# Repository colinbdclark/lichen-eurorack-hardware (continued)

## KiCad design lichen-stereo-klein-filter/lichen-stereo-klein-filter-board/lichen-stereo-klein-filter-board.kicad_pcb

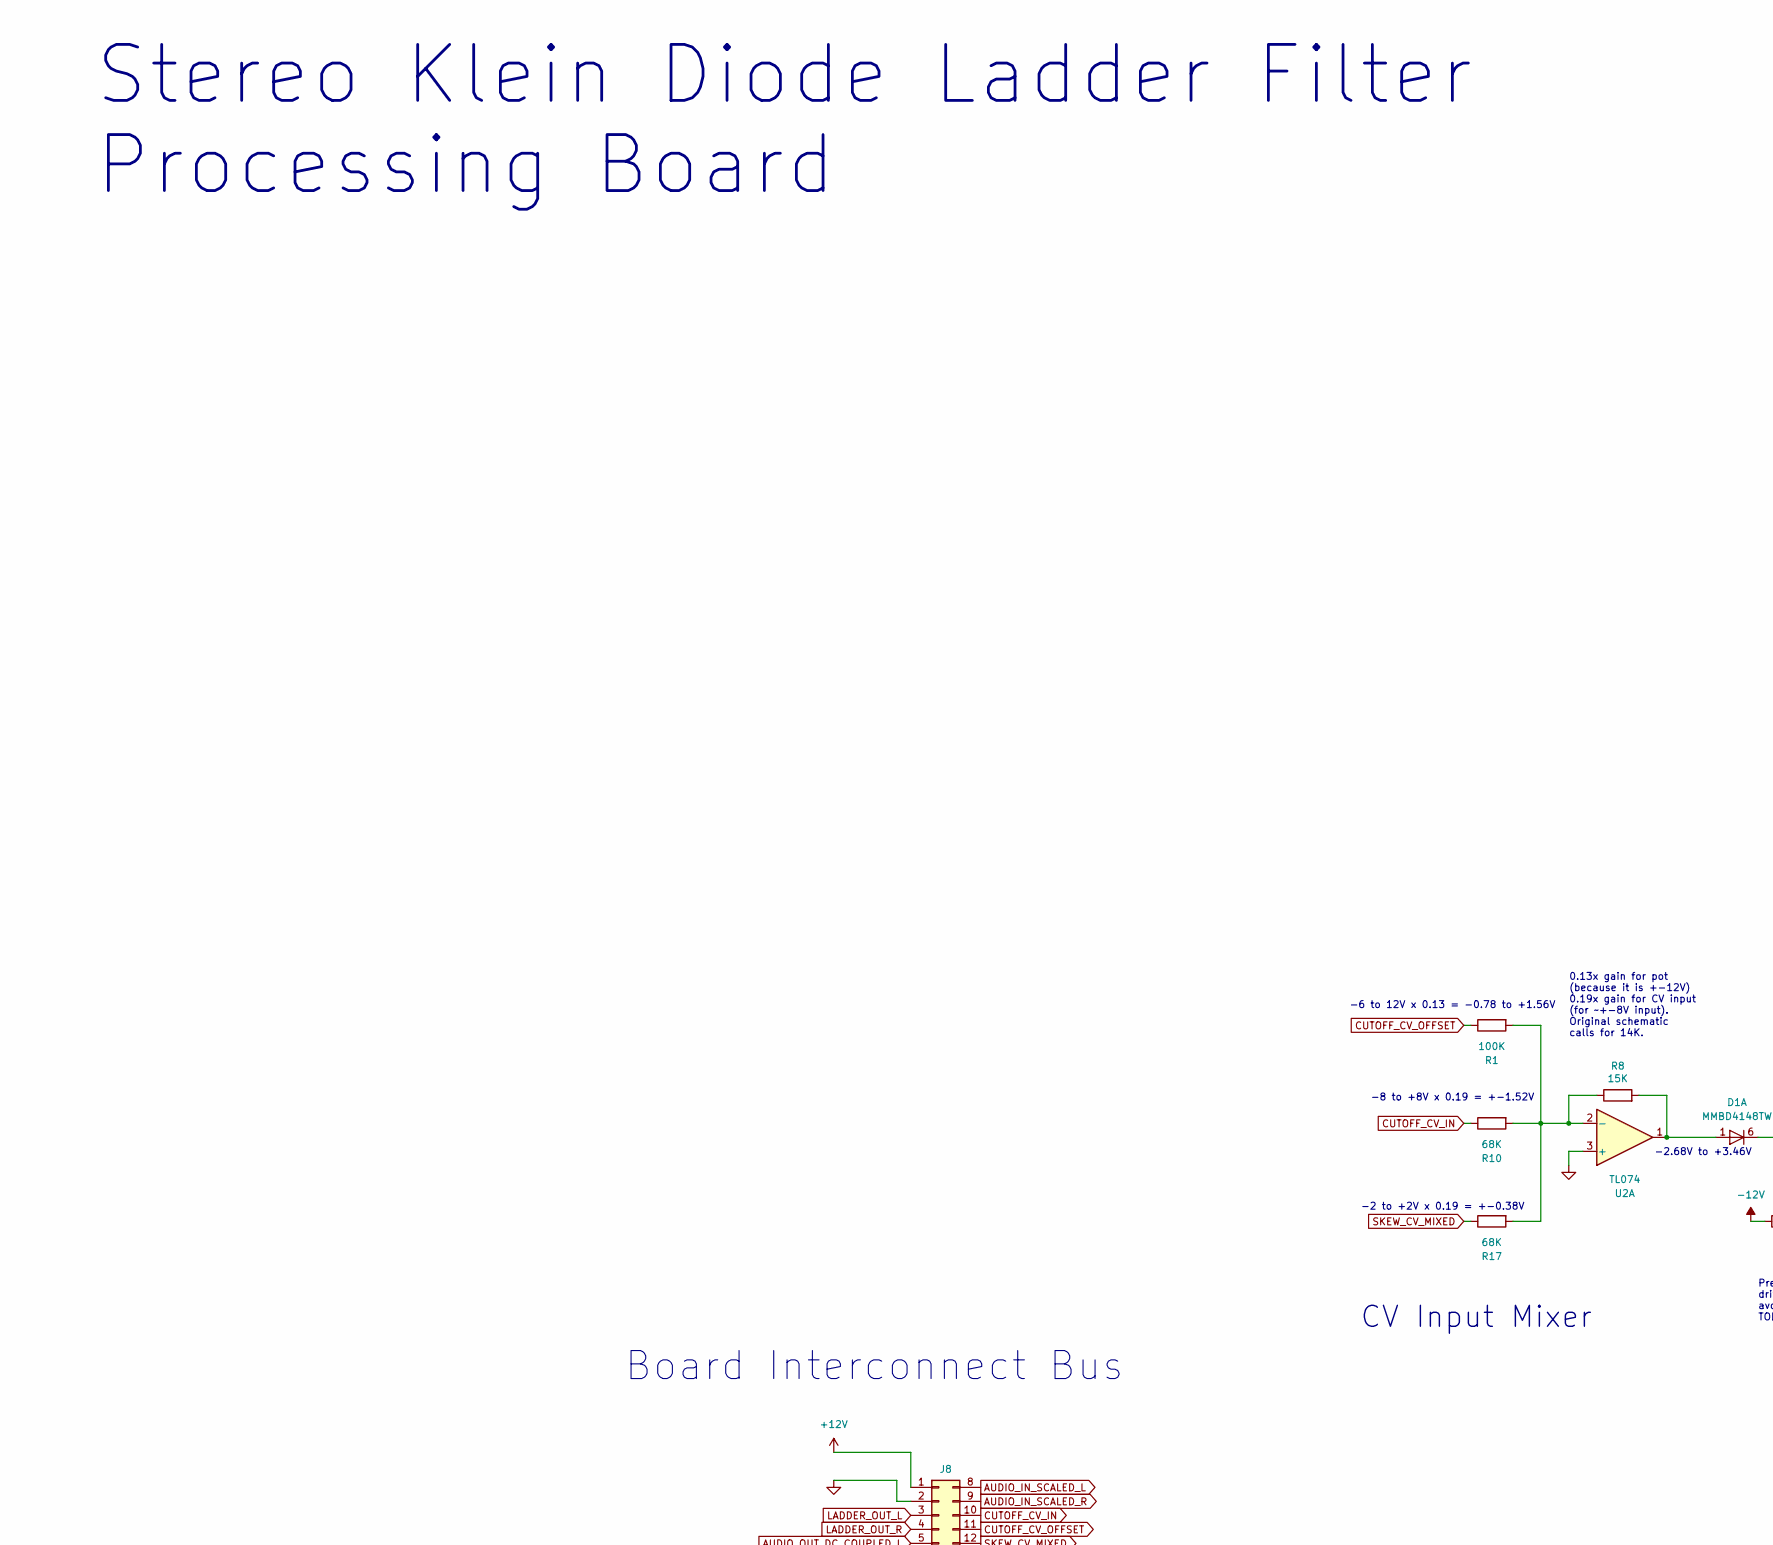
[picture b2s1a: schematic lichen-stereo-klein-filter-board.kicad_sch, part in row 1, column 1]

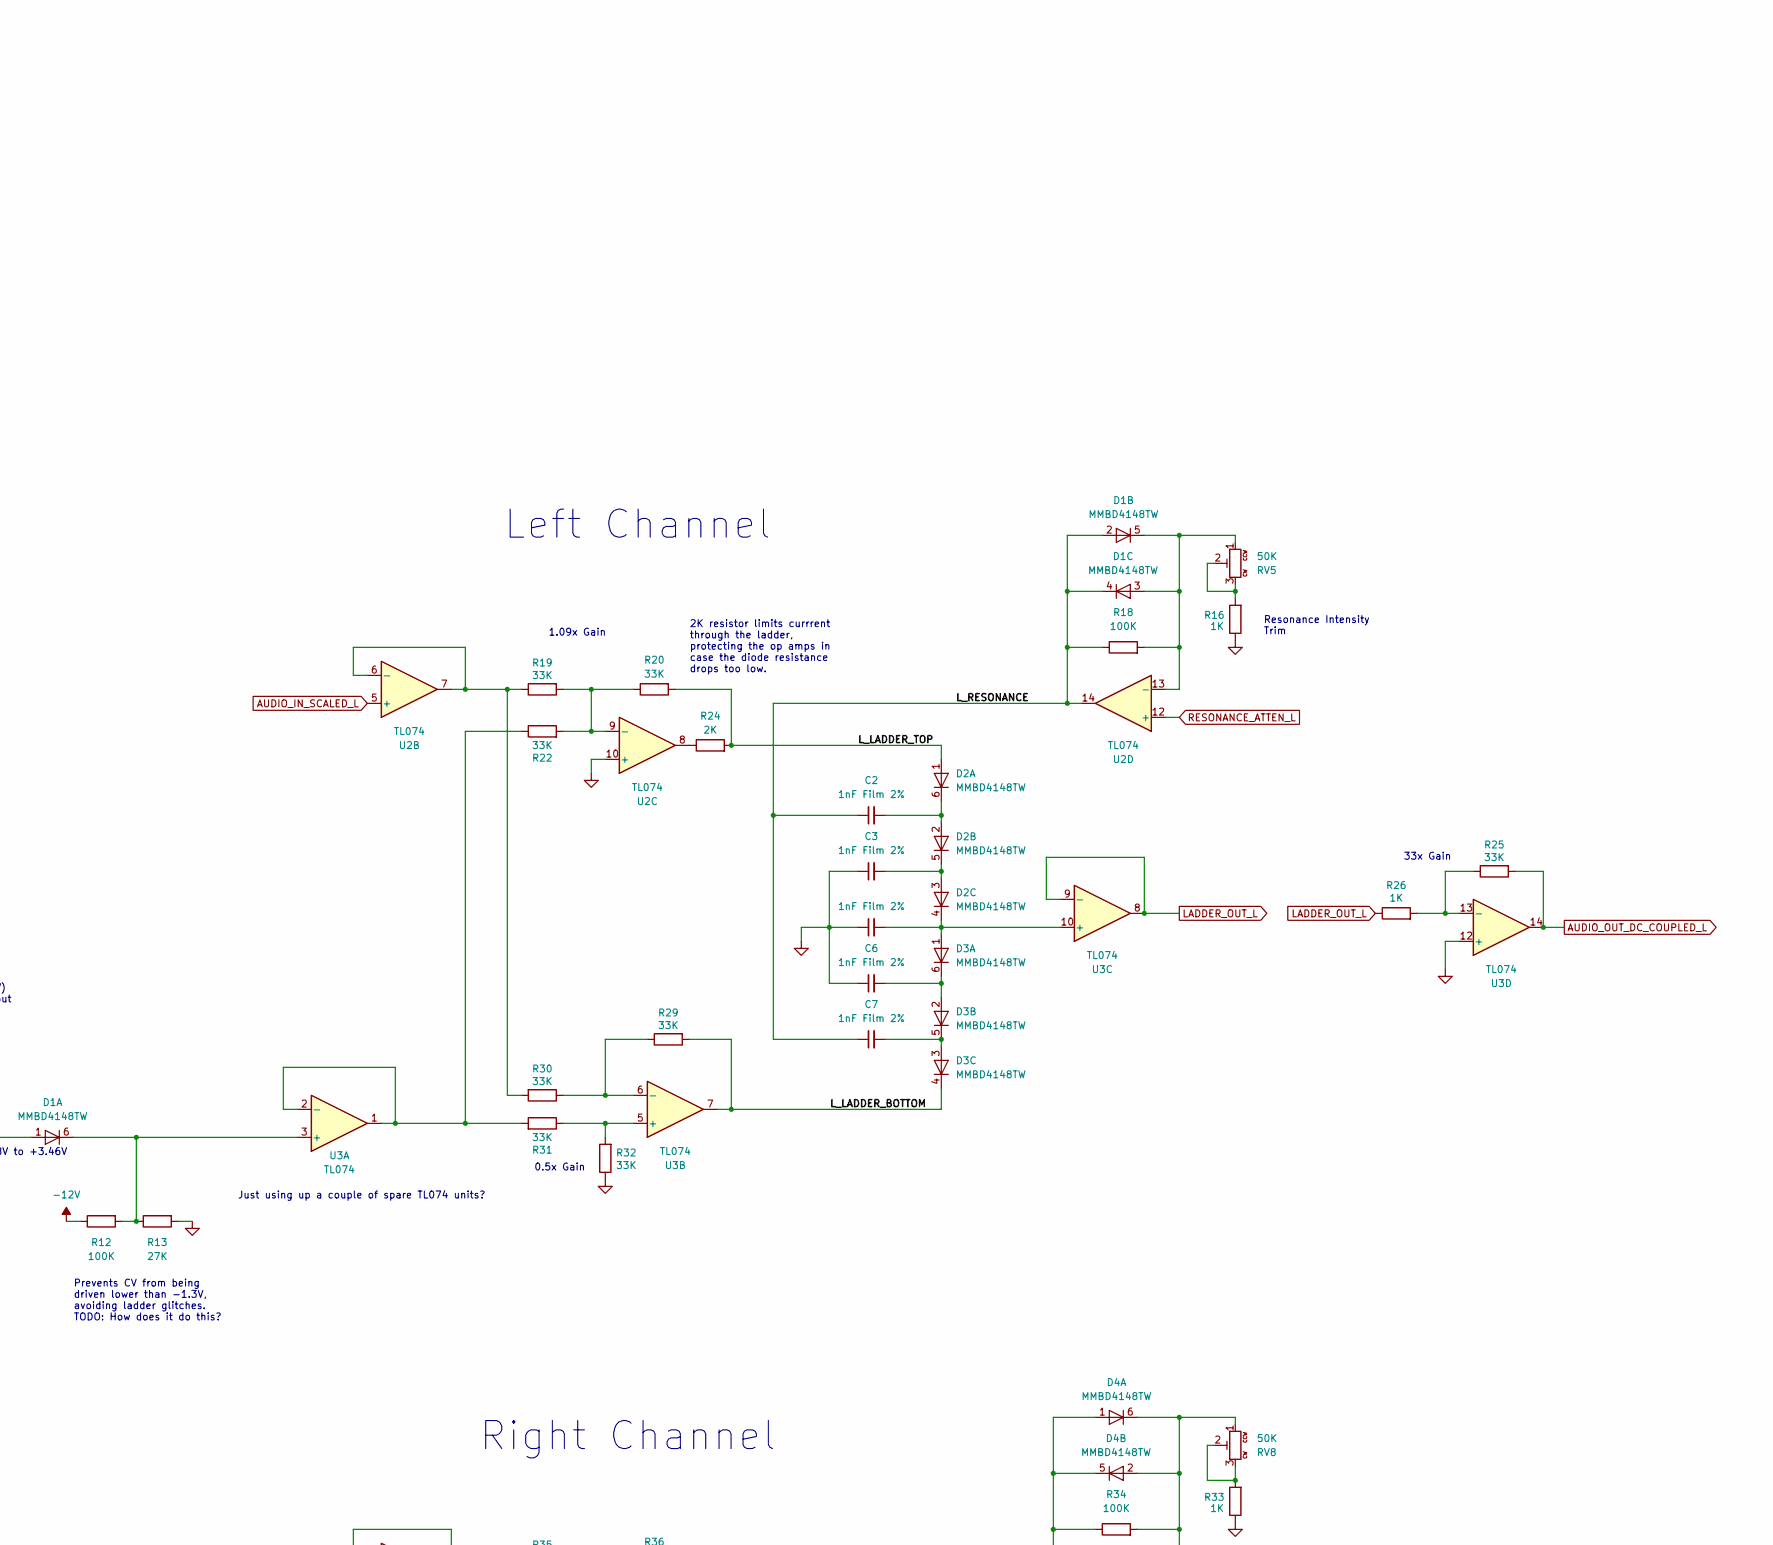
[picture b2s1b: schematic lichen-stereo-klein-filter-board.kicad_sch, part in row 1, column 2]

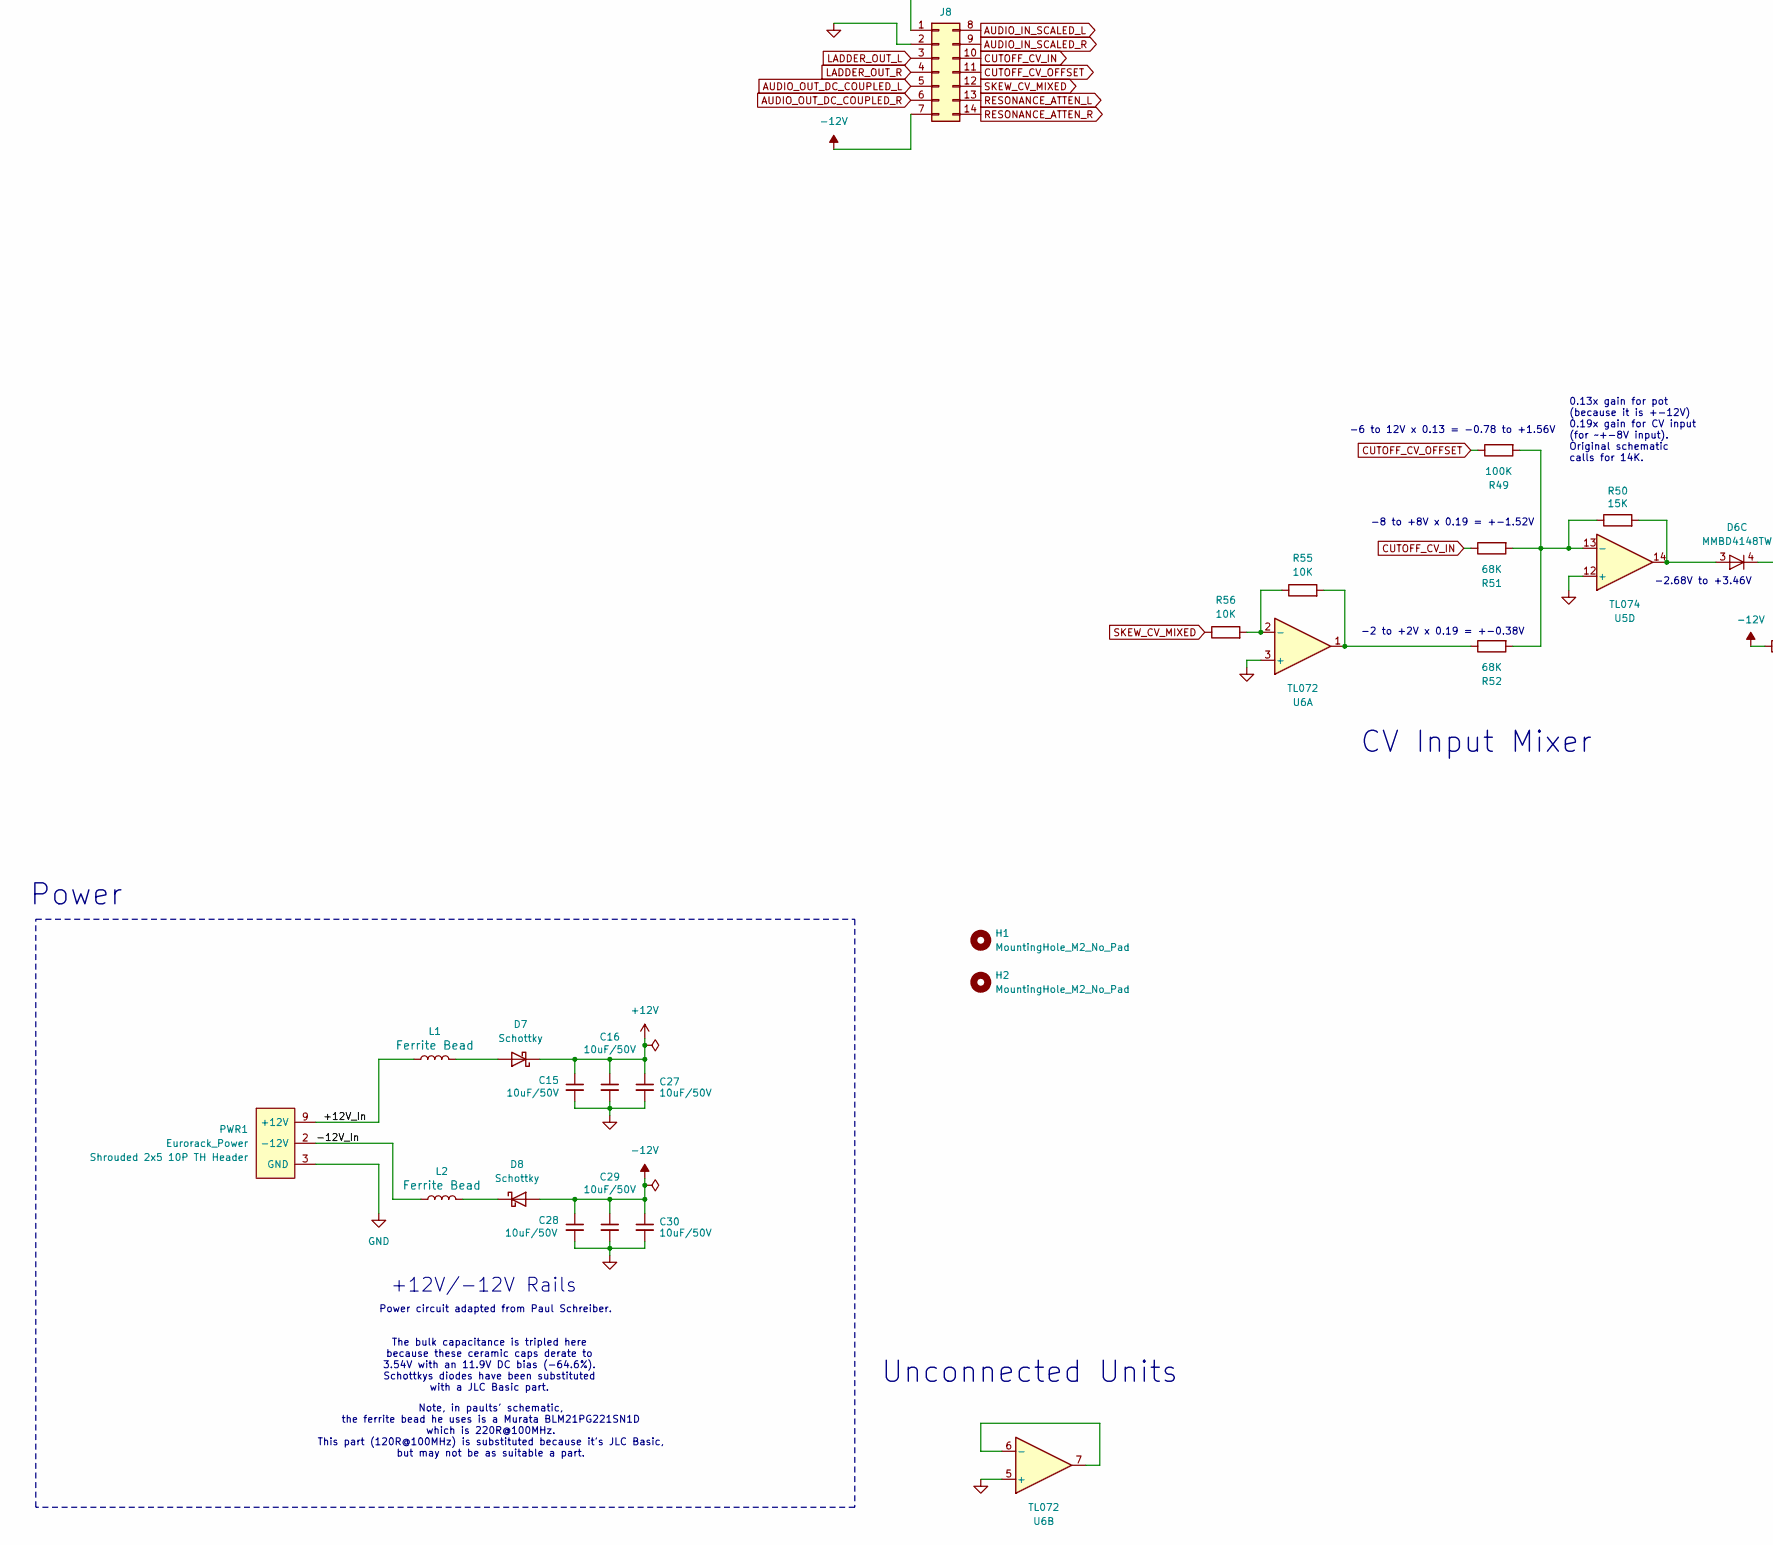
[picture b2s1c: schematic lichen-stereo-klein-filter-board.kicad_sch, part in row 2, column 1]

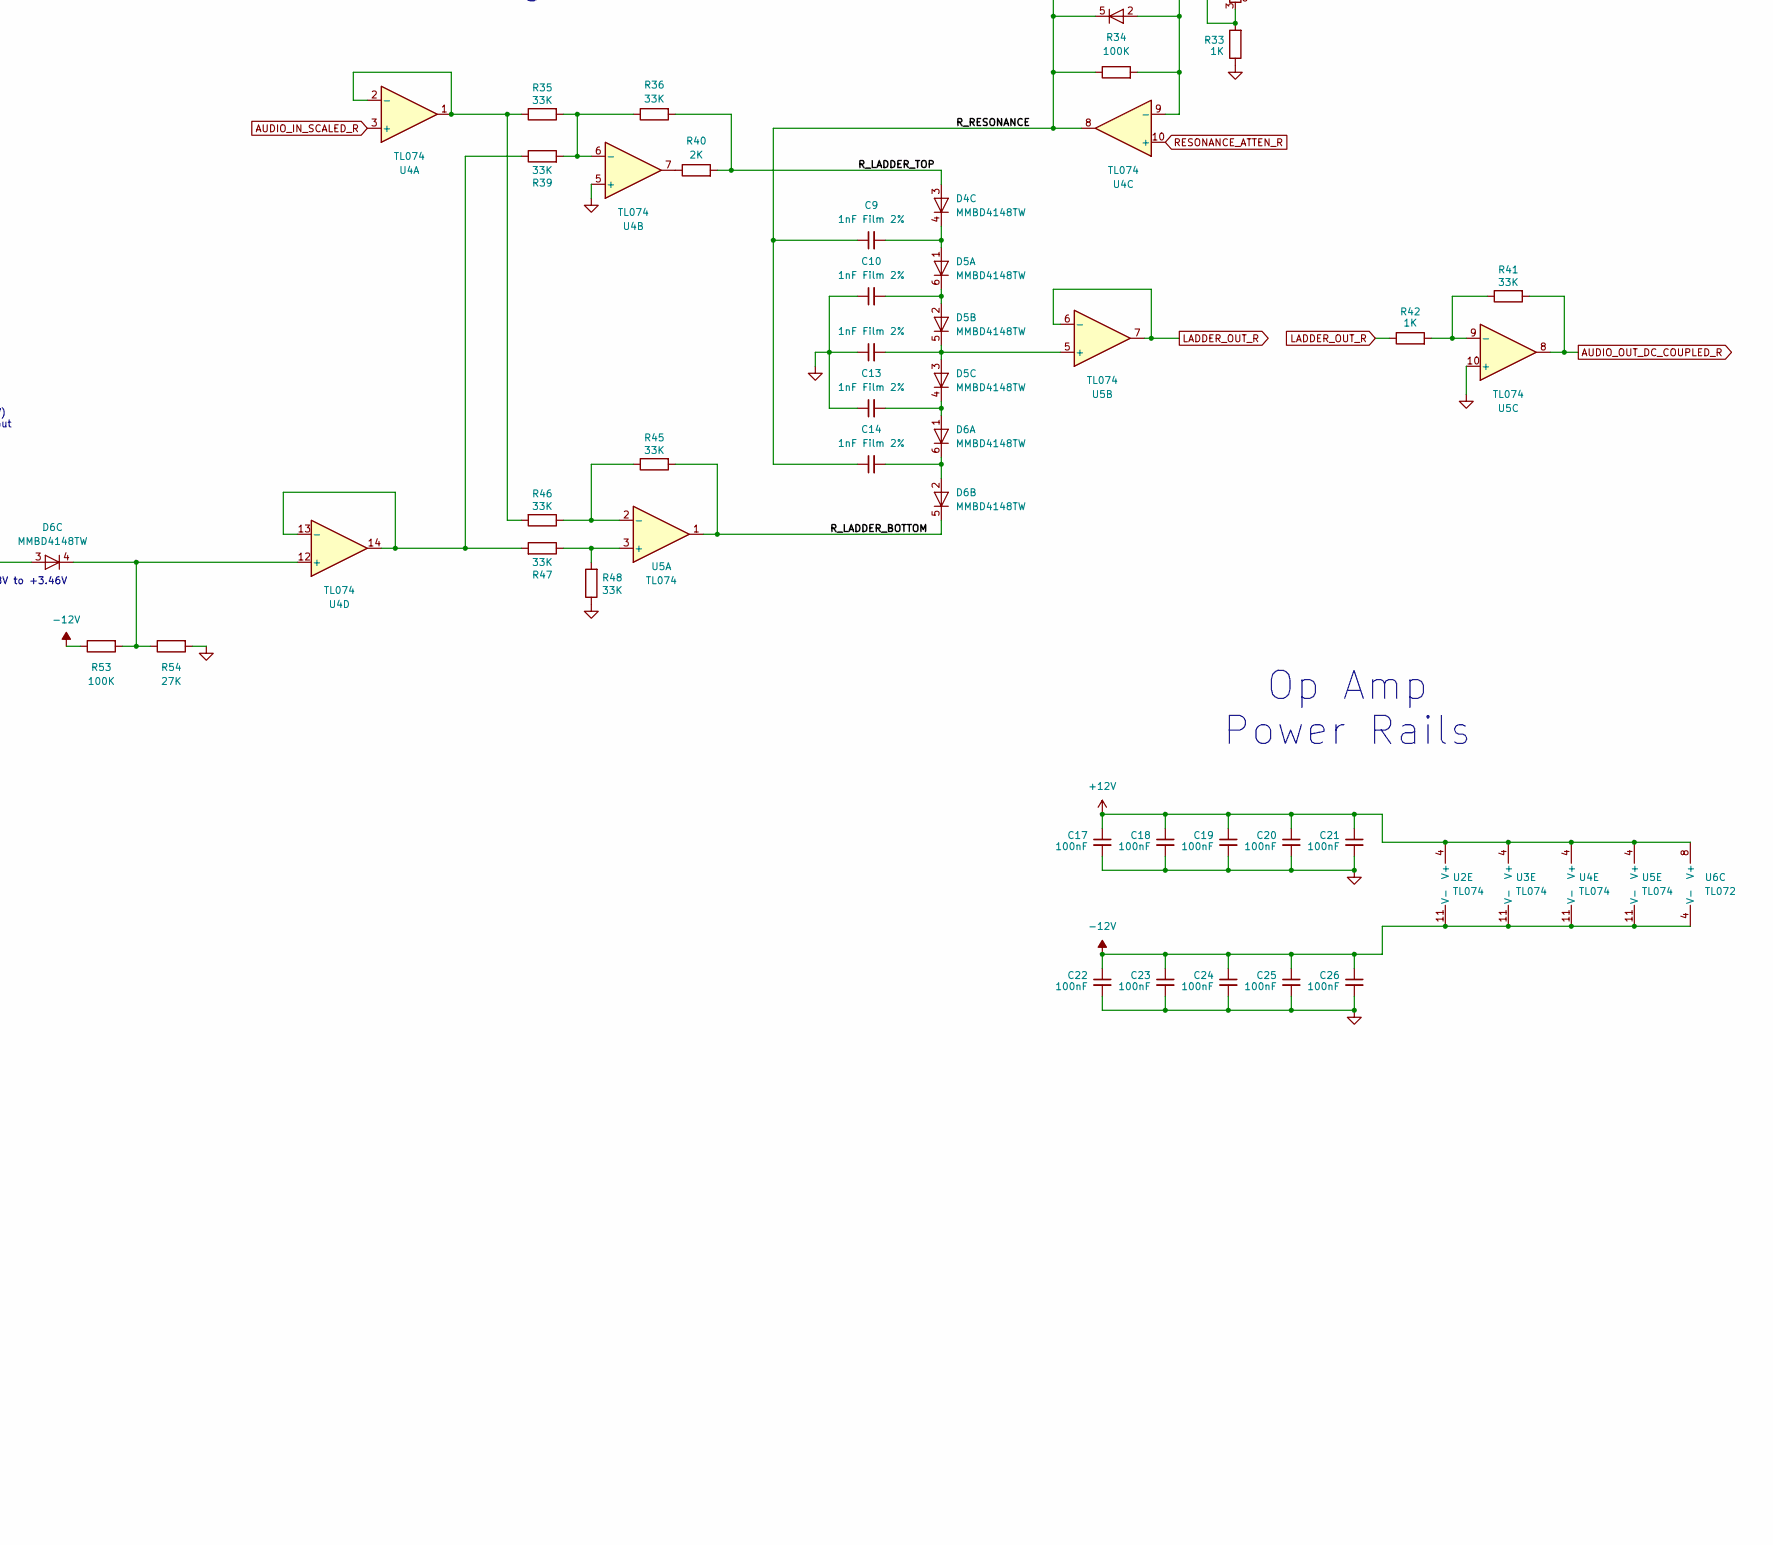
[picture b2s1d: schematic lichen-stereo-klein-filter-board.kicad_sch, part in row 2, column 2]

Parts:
C2, C3, C4, C6, C7, C9, C10, C11, C13, C14: 1nF; C_0805; Part Number ECHU1H102GX5; LCSC C569826
C15, C16, C27, C28, C29, C30: 10uF; C_1206_3216Metric; Part Number CL31A106KBHNNNE; LCSC C13585
C17, C18, C19, C20, C21, C22, C23, C24, C25, C26: 100nF; C_0402_1005Metric_small_pads; Part Number CL05B104KB54PNC; LCSC C307331
D1, D2, D3, D4, D5, D6: MMBD4148TW; SOT-363_SC-70-6; Part Number MMBD4148TW; LCSC C5240652
D7, D8: Schottky; D_SMA_Handsoldering; Part Number SS34; LCSC C8678
H1, H2: MountingHole_M2_No_Pad; MountingHole_2.2mm_M2
J8: 02x07 Pins; PinHeader_2x07_P2.54mm_Vertical_SMD; Part Number 2.54-2*7P针立贴; LCSC C84004
L1, L2: FerriteBead_0603_2A; R_0603; Part Number BLM18PG121SN1D; LCSC C14709
PWR1: Eurorack_Power; Eurorack_Power_Shrouded_TH_Staggered_Small
R1, R12, R18, R34, R49, R53: 100K; R_0603; Part Number 0603WAF1003T5E; LCSC C25803
R8, R50: 15K; R_0603; Part Number 0603WAF1502T5E; LCSC C22809
R10, R17, R51, R52: 68K; R_0603; Part Number 0603WAF6802T5E; LCSC C23231
R13, R54: 27K; R_0603; Part Number 0603WAF2702T5E; LCSC C22967
R16, R26, R33, R42: 1K; R_0603; Part Number 0603WAF1001T5E; LCSC C21190
R19, R20, R22, R25, R29, R30, R31, R32, R35, R36, R39, R41, R45, R46, R47, R48: 33K; R_0603; Part Number 0603WAF3302T5E; LCSC C4216
R24, R40: 2K; R_0603; Part Number 0603WAF2001T5E; LCSC C22975
R55, R56: 10K; R_0603; Part Number 0603WAF1002T5E; LCSC C25804
RV5, RV8: 50K; Potentiometer_Bourns_3266W_Vertical; Part Number 3266W-1-503LF; LCSC C780226
U2, U3, U4, U5: TL074; SOIC-14_3.9x8.7mm_P1.27mm; Part Number TL074IDR; LCSC C6964
U6: TL072; SOIC-8_3.9x4.9mm_P1.27mm; Part Number TL072CDT; LCSC C6961

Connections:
+12V: C15.1, C16.1, C17.1, C18.1, C19.1, C20.1, C21.1, C27.1, D7.1 (K), J8.1, U2.4 (V+), U3.4 (V+), U4.4 (V+), U5.4 (V+), U6.8 (V+)
-12V: C22.1, C23.1, C24.1, C25.1, C26.1, C28.1, C29.1, C30.1, D8.2 (A), J8.7, R12.1, R53.1, U2.11 (V-), U3.11 (V-), U4.11 (V-), U5.11 (V-), U6.4 (V-)
/+12V_In: L1.1, PWR1.9 (+12V), PWR1.10 (+12V)
/-12V_In: L2.1, PWR1.1 (-12V), PWR1.2 (-12V)
/L_LADDER_BOTTOM: D3.4 (K), R29.2, U3.7
/L_LADDER_TOP: D2.1 (A), R20.2, R24.2
/L_RESONANCE: C2.1, C7.1, D1.2 (A), D1.4 (K), R18.1, U2.14
/R_LADDER_BOTTOM: D6.5 (K), R45.2, U5.1
/R_LADDER_TOP: D4.3 (A), R36.2, R40.2
/R_RESONANCE: C9.1, C14.1, D4.1 (A), D4.5 (K), R34.1, U4.8
AUDIO_IN_SCALED_L: J8.8, U2.5 (+)
AUDIO_IN_SCALED_R: J8.9, U4.3 (+)
AUDIO_OUT_DC_COUPLED_L: J8.5, R25.2, U3.14
AUDIO_OUT_DC_COUPLED_R: J8.6, R41.2, U5.8
CUTOFF_CV_IN: J8.10, R10.1, R51.1
CUTOFF_CV_OFFSET: J8.11, R1.1, R49.1
GND: C3.1, C4.1, C6.1, C10.1, C11.1, C13.1, C15.2, C16.2, C17.2, C18.2, C19.2, C20.2, C21.2, C22.2, C23.2, C24.2, C25.2, C26.2, C27.2, C28.2, C29.2, C30.2, J8.2, PWR1.3 (GND), PWR1.4 (GND), PWR1.5 (GND), PWR1.6 (GND), PWR1.7 (GND), PWR1.8 (GND), R13.2, R16.1, R32.1, R33.1, R48.1, R54.2, U2.3 (+), U2.10 (+), U3.12 (+), U4.5 (+), U5.10 (+), U5.12 (+), U6.3 (+), U6.5 (+)
LADDER_OUT_L: J8.3, R26.1, U3.8, U3.9 (-)
LADDER_OUT_R: J8.4, R42.1, U5.6 (-), U5.7
unnamed: D1.1 (A), R8.2, U2.1
unnamed: D1.6 (K), R12.2, R13.1, U3.3 (+)
unnamed: D1.3 (A), D1.5 (K), R18.2, RV5.1, U2.13 (-)
unnamed: C2.2, D2.2 (A), D2.6 (K)
unnamed: C3.2, D2.3 (A), D2.5 (K)
unnamed: C4.2, D2.4 (K), D3.1 (A), U3.10 (+)
unnamed: C6.2, D3.2 (A), D3.6 (K)
unnamed: C7.2, D3.3 (A), D3.5 (K)
unnamed: D4.2 (A), D4.6 (K), R34.2, RV8.1, U4.9 (-)
unnamed: C9.2, D4.4 (K), D5.1 (A)
unnamed: C10.2, D5.2 (A), D5.6 (K)
unnamed: C11.2, D5.3 (A), D5.5 (K), U5.5 (+)
unnamed: C13.2, D5.4 (K), D6.1 (A)
unnamed: C14.2, D6.2 (A), D6.6 (K)
unnamed: D6.3 (A), R50.2, U5.14
unnamed: D6.4 (K), R53.2, R54.1, U4.12 (+)
unnamed: D7.2 (A), L1.2
unnamed: D8.1 (K), L2.2
unnamed: R16.2, RV5.2, RV5.3
unnamed: R24.1, U2.8
unnamed: R33.2, RV8.2, RV8.3
unnamed: R40.1, U4.7
unnamed: R52.1, R55.2, U6.1
unnamed: R1.2, R8.1, R10.2, R17.2, U2.2 (-)
unnamed: R19.1, R30.2, U2.6 (-), U2.7
unnamed: R19.2, R20.1, R22.2, U2.9 (-)
unnamed: R22.1, R31.2, U3.1, U3.2 (-)
unnamed: R31.1, R32.2, U3.5 (+)
unnamed: R29.1, R30.1, U3.6 (-)
unnamed: R25.1, R26.2, U3.13 (-)
unnamed: R35.1, R46.2, U4.1, U4.2 (-)
unnamed: R35.2, R36.1, R39.2, U4.6 (-)
unnamed: R39.1, R47.2, U4.13 (-), U4.14
unnamed: R47.1, R48.2, U5.3 (+)
unnamed: R45.1, R46.1, U5.2 (-)
unnamed: R41.1, R42.2, U5.9 (-)
unnamed: R49.2, R50.1, R51.2, R52.2, U5.13 (-)
unnamed: R55.1, R56.2, U6.2 (-)
unnamed: U6.6 (-), U6.7
RESONANCE_ATTEN_L: J8.13, U2.12 (+)
RESONANCE_ATTEN_R: J8.14, U4.10 (+)
SKEW_CV_MIXED: J8.12, R17.1, R56.1

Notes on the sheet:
-8 to +8V x 0.19 = +-1.52V
-2.68V to +3.46V
CV Input Mixer
Prevents CV from being driven lower than -1.3V, avoiding ladder glitches. TODO: How does it do this?
Board Interconnect Bus
0.13x gain for pot (because it is +-12V) 0.19x gain for CV input (for ~+-8V input). Original schematic calls for 14K.
The bulk capacitance is tripled here because these ceramic caps derate to 3.54V with an 11.9V DC bias (-64.6%). Schottkys diodes have been substituted with a JLC Basic part.
Right Channel
Op Amp Power Rails
Resonance Intensity Trim
0.5x Gain
-2 to +2V x 0.19 = +-0.38V
1.09x Gain
+12V/-12V Rails
-6 to 12V x 0.13 = -0.78 to +1.56V
33x Gain
Unconnected Units
Power
Stereo Klein Diode Ladder Filter Processing Board
Left Channel
Just using up a couple of spare TL074 units?
Note, in paults' schematic, the ferrite bead he uses is a Murata BLM21PG221SN1D which is 220R@100MHz. This part (120R@100MHz) is substituted because it's JLC Basic, but may not be as suitable a part.
Power circuit adapted from Paul Schreiber.
2K resistor limits currrent through the ladder, protecting the op amps in case the diode resistance drops too low.

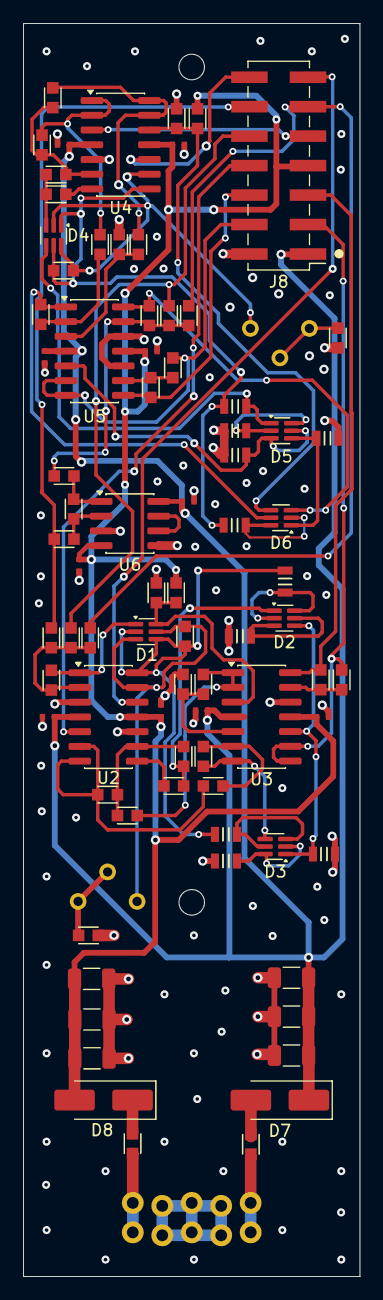
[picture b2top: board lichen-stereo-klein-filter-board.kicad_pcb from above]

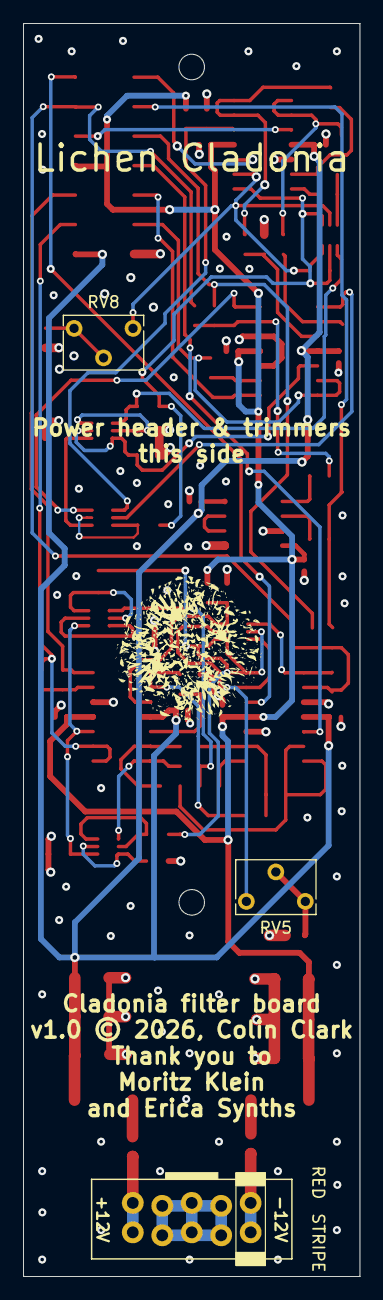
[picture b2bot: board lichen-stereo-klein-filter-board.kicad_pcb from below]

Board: 4 copper layers, 29.0 x 108.0 mm, 85 parts (5 on the bottom side), 61 nets.

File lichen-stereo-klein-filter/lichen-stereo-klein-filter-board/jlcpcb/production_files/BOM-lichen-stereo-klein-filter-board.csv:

Comment,Designator,Footprint,LCSC,Quantity
10uF,"C15,C16,C27,C28,C29,C30",C_1206_3216Metric,C13585,6
FerriteBead_0603_2A,"L1,L2",R_0603,C14709,2
1K,"R16,R26,R33,R42",R_0603,C21190,4
15K,"R50,R8",R_0603,C22809,2
27K,"R13,R54",R_0603,C22967,2
2K,"R24,R40",R_0603,C22975,2
68K,"R10,R17,R51,R52",R_0603,C23231,4
100K,"R1,R12,R18,R34,R49,R53",R_0603,C25803,6
10K,"R55,R56",R_0603,C25804,2
100nF,"C17,C18,C19,C20,C21,C22,C23,C24,C25,C26",C_0402_1005Metric_small_pads,C307331,10
33K,"R19,R20,R22,R25,R29,R30,R31,R32,R35,R36,R39,R41,R45,R46,R47,R48",R_0603,C4216,16
MMBD4148TW,"D1,D2,D3,D4,D5,D6",SOT-363_SC-70-6,C5240652,6
1nF,"C10,C11,C13,C14,C2,C3,C4,C6,C7,C9",C_0805,C569826,10
TL072,U6,SOIC-8_3.9x4.9mm_P1.27mm,C6961,1
TL074,"U2,U3,U4,U5",SOIC-14_3.9x8.7mm_P1.27mm,C6964,4
02x07 Pins,J8,PinHeader_2x07_P2.54mm_Vertical_SMD,C84004,1
Schottky,"D7,D8",D_SMA_Handsoldering,C8678,2

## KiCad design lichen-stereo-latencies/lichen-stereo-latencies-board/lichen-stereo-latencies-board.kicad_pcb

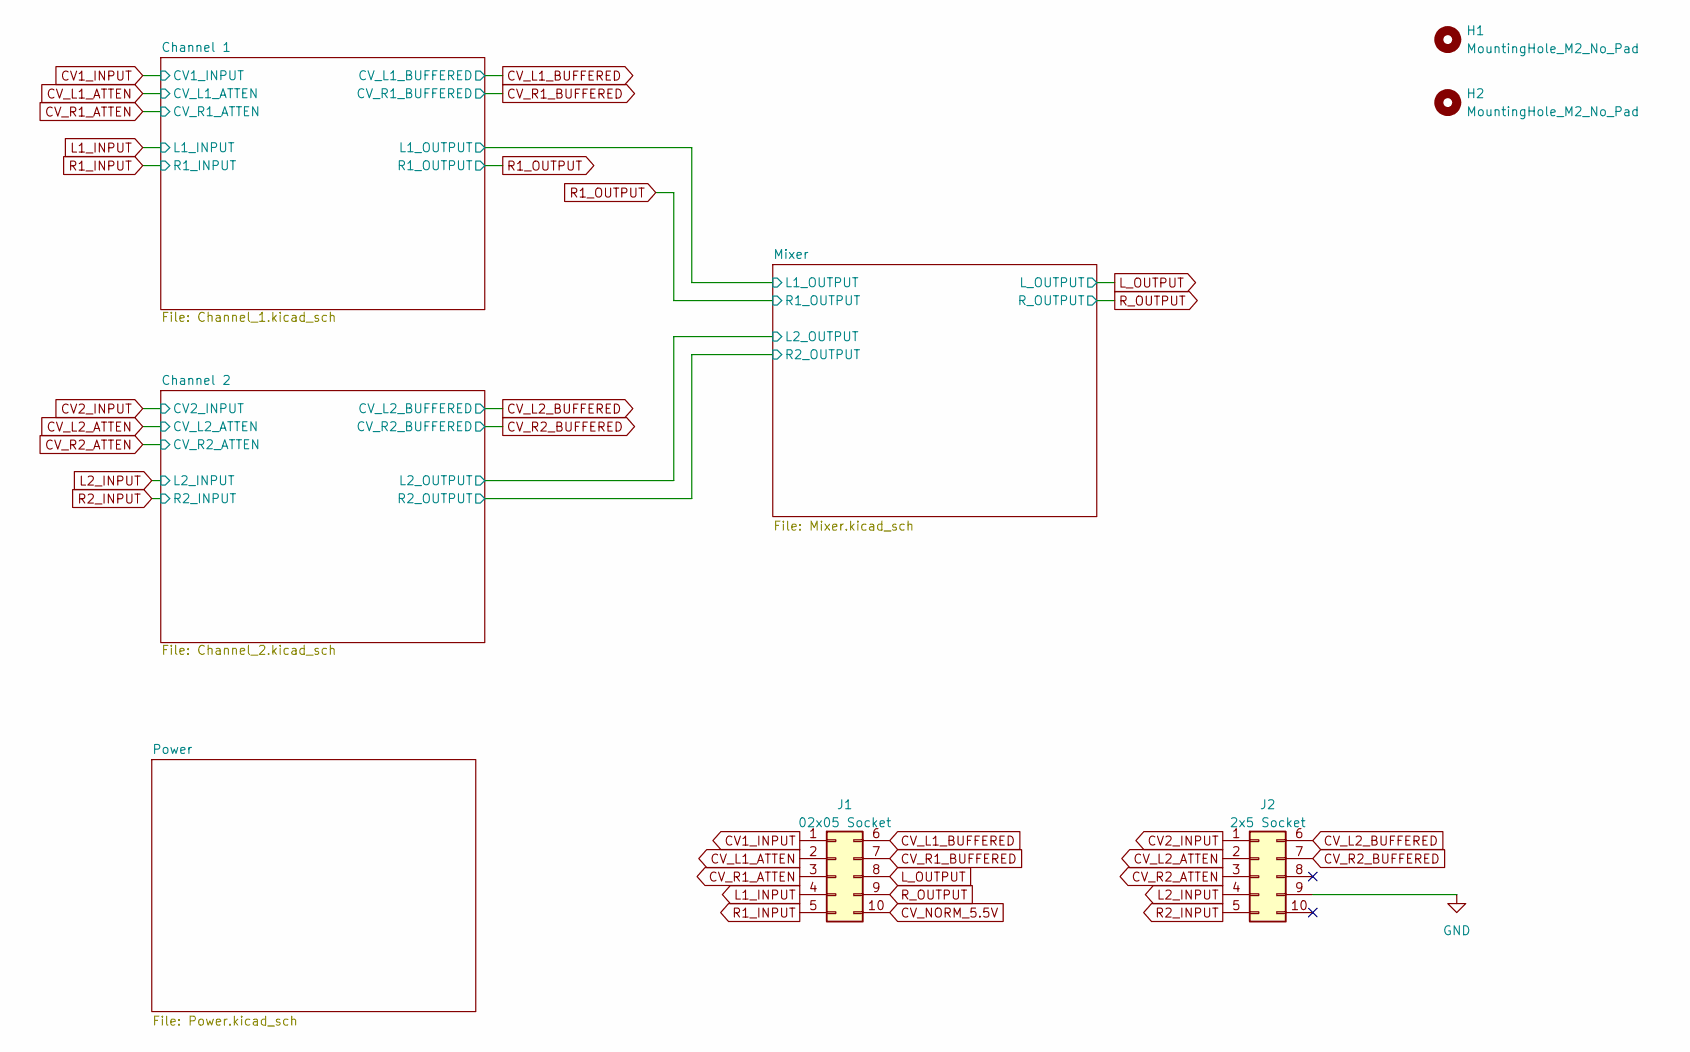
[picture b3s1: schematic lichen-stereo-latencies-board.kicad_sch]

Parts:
H1, H2: MountingHole_M2_No_Pad; MountingHole_2.2mm_M2
J1: 02x05 Socket; PinSocket_2x05_P2.54mm_Vertical
J2: 2x5 Socket; PinSocket_2x05_P2.54mm_Vertical

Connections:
CV1_INPUT: J1.1; also elsewhere on the board
CV2_INPUT: J2.1; also elsewhere on the board
CV_L1_ATTEN: J1.2; also elsewhere on the board
CV_L1_BUFFERED: J1.6; also elsewhere on the board
CV_L2_ATTEN: J2.2; also elsewhere on the board
CV_L2_BUFFERED: J2.6; also elsewhere on the board
CV_NORM_5.5V: J1.10; also elsewhere on the board
CV_R1_ATTEN: J1.3; also elsewhere on the board
CV_R1_BUFFERED: J1.7; also elsewhere on the board
CV_R2_ATTEN: J2.3; also elsewhere on the board
CV_R2_BUFFERED: J2.7; also elsewhere on the board
GND: J2.9; also elsewhere on the board
L1_INPUT: J1.4; also elsewhere on the board
L2_INPUT: J2.4; also elsewhere on the board
L_OUTPUT: J1.8; also elsewhere on the board
R1_INPUT: J1.5; also elsewhere on the board
R2_INPUT: J2.5; also elsewhere on the board
R_OUTPUT: J1.9; also elsewhere on the board

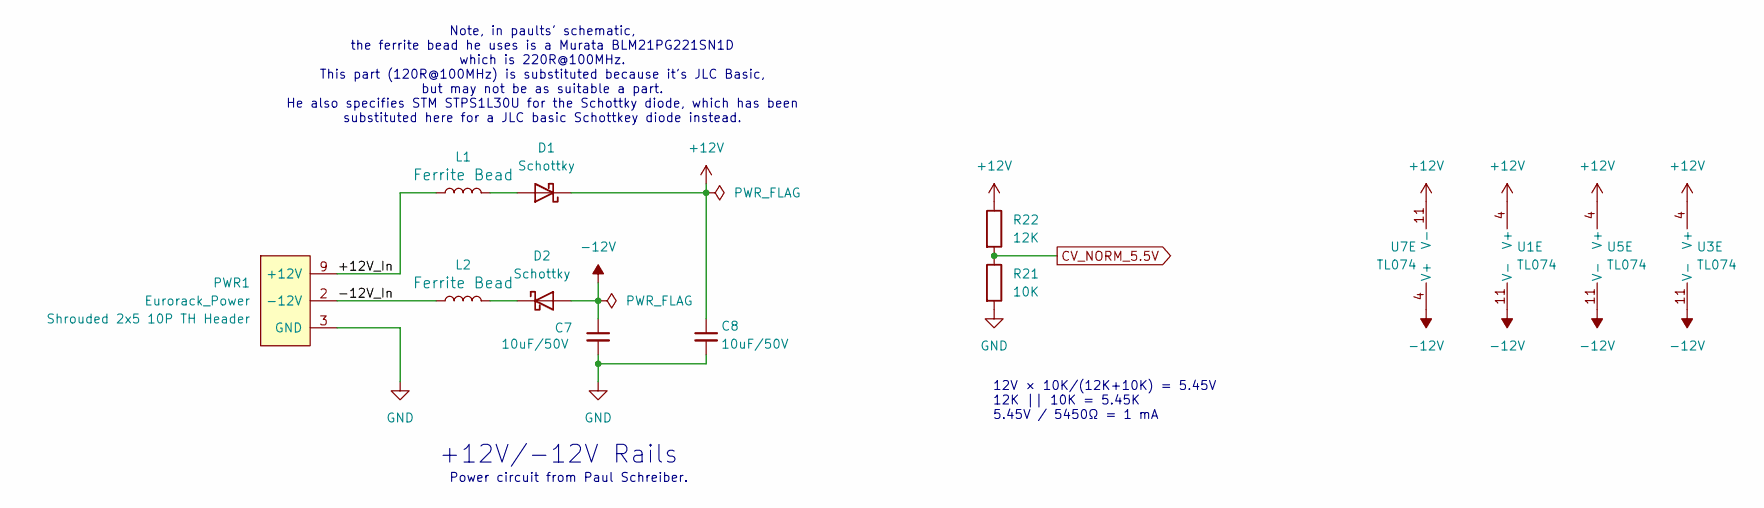
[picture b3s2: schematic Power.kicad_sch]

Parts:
C7, C8: 10uF; C_0805; Part Number GRM21BR61H106KE43L; LCSC C440198
D1, D2: Schottky; D_SMA_Handsoldering; Part Number SS34; LCSC C8678
L1, L2: FerriteBead_0603_2A; R_0603; Part Number BLM18PG121SN1D; LCSC C14709
PWR1: Eurorack_Power; Eurorack_Power_Shrouded_TH_Staggered_Small
R21: 10K; R_0402_1005Metric; Part Number 0402WGF1002TCE; LCSC C25744
R22: 12K; R_0402_1005Metric; Part Number 0402WGF1202TCE; LCSC C25752
U1, U3, U5, U7: TL074; SOIC-14_3.9x8.7mm_P1.27mm; Part Number TL074IDR; LCSC C6964

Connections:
+12V: C8.1, D1.1 (K), R22.1, U1.4 (V+), U3.4 (V+), U5.4 (V+), U7.11 (V-)
-12V: C7.1, D2.2 (A), U1.11 (V-), U3.11 (V-), U5.11 (V-), U7.4 (V+)
/Power/+12V_In: L1.1, PWR1.9 (+12V), PWR1.10 (+12V)
/Power/-12V_In: L2.1, PWR1.1 (-12V), PWR1.2 (-12V)
CV_NORM_5.5V: R21.1, R22.2; also elsewhere on the board
GND: C7.2, C8.2, PWR1.3 (GND), PWR1.4 (GND), PWR1.5 (GND), PWR1.6 (GND), PWR1.7 (GND), PWR1.8 (GND), R21.2; also elsewhere on the board
unnamed: D1.2 (A), L1.2
unnamed: D2.1 (K), L2.2

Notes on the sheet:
12V × 10K/(12K+10K) = 5.45V 12K || 10K = 5.45K 5.45V / 5450Ω = 1 mA
Power circuit from Paul Schreiber.
Note, in paults' schematic, the ferrite bead he uses is a Murata BLM21PG221SN1D which is 220R@100MHz. This part (120R@100MHz) is substituted because it's JLC Basic, but may not be as suitable a part. He also specifies STM STPS1L30U for the Schottky diode, which has been substituted here for a JLC b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
+12V/-12V Rails

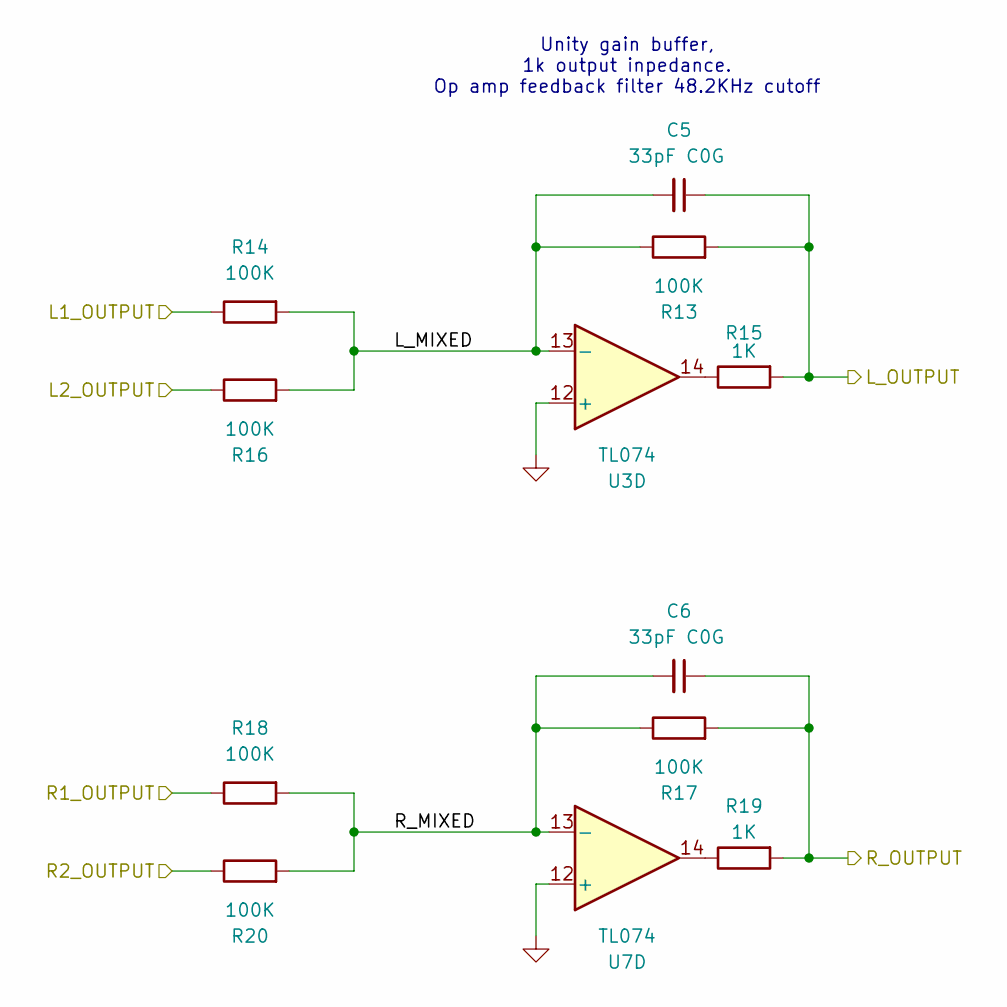
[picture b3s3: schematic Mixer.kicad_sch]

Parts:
C5, C6: 33pF C0G; C_0603; Part Number CL10C330JB8NNNC; LCSC C1663
R13, R14, R16, R17, R18, R20: 100K; R_0402_1005Metric; Part Number 0402WGF1003TCE; LCSC C25741
R15, R19: 1K; R_0402_1005Metric; Part Number 0402WGF1001TCE; LCSC C11702
U3, U7: TL074; SOIC-14_3.9x8.7mm_P1.27mm; Part Number TL074IDR; LCSC C6964

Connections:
/Channel 1/L1_OUTPUT: R14.1; also elsewhere on the board
/Channel 2/L2_OUTPUT: R16.1; also elsewhere on the board
/Channel 2/R2_OUTPUT: R20.1; also elsewhere on the board
/Mixer/L_MIXED: C5.2, R13.1, R14.2, R16.2, U3.13 (-)
/Mixer/R_MIXED: C6.2, R17.1, R18.2, R20.2, U7.13 (-)
GND: U3.12 (+), U7.12 (+); also elsewhere on the board
L_OUTPUT: C5.1, R13.2, R15.2; also elsewhere on the board
unnamed: R15.1, U3.14
unnamed: R19.1, U7.14
R1_OUTPUT: R18.1; also elsewhere on the board
R_OUTPUT: C6.1, R17.2, R19.2; also elsewhere on the board

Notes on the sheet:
Unity gain buffer, 1k output inpedance. Op amp feedback filter 48.2KHz cutoff
